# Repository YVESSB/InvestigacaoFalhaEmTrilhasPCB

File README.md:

# Identificação de curto-circuito em circuito impresso utilizando ESPECTROSCOPIA DE IMPEDÂNICA ELÉTRICA

Palavras-chave:
 * ESPECTROSCOPIA DE IMPEDÂNICA ELÉTRICA
 * DETECÇÃO DE FALHAS
 * PLACA DE CIRCUITO IMPRESSO - PCI | PCB

Nesta página são fornecidos dados e documentos referente a análise de dados. Informações utilizadas no trabalho de mestrado e com o objetivo de identificar potencial curto-circuito em um circuito impresso, por meio da espectroscopia de impedância elétrica

Observações:

* Para os programas disponíveis na pasta '2 - Programas', os arquivos de dados devem estar no mesmo ambiente (disponíveis em '1 - DadosAnalisados').
* Programas desenvolvidos em Python, com Jupyter Notebook.

## Introdução 

Para o a identificação de possíveis curto-circuito utilizando a espectroscopia de impedância elétrica, diferentes trilhas em placas de circuito impresso foram medidas utilizando um espectrômetro.

<div align="center">

</div>

As trilhas medidas estavam em placas de circuitos impresso feita de fenolite, e que tinham parâmetros alterados de em função de comprimento, distancia de isolamento e nível do potencial curto-circuito.

<div align="center">

</div>

## Resultados

### Análise qualitativa com gráficos de Bode e dendrogramas
Os dados obtidos das medições foram fundamental para a validaçãode que a espectroscopia pode ser utilizada como técnica para identificação de potenciais curtos-circuitos em placas de circuito impresso (PCIs ou PCBs), por meio da análise qualitativa ou quantitativa. A seguir são apresentado gráficos de dispersão e dendrograma das medições de trilhas de espessura de 0,75mm e isolamento de 1,5mm, onde é possível identificar que há um  agrupamento e tendência da separação de trilhas com potenciais curto-circuito em comparação a uma trilha sem defeito.

<div align="center">

</div>

### Análise quantitativa por meio de algoritmos - aprendizado de máquina
 Com os dados obtidos, foram quasificados dados de trilhas SEM falhas e COM falhas. Se tratamdo de dados advindos de um problema multivariável, a constatação de correlação por aprendizado de máquina é uma solução, para validação de problemas.

<div align="center">

</div>

## Referência

* BORGES, Yves Santos. Análise de curto-circuito em trilhas de circuito impresso utilizando espectroscopia de impedância elétrica. 2023. 1 recurso on-line (70 p. Dissertação (Mestrado Profissional)-Universidade do Estado de Santa Catarina, Programa de Pós-Graduação em Engenharia Elétrica, 2023. Disponível em: http://sistemabu.udesc.br/pergamumweb/vinculos/0000b5/0000b540.pdf. Acesso em: 21 nov. 2023.

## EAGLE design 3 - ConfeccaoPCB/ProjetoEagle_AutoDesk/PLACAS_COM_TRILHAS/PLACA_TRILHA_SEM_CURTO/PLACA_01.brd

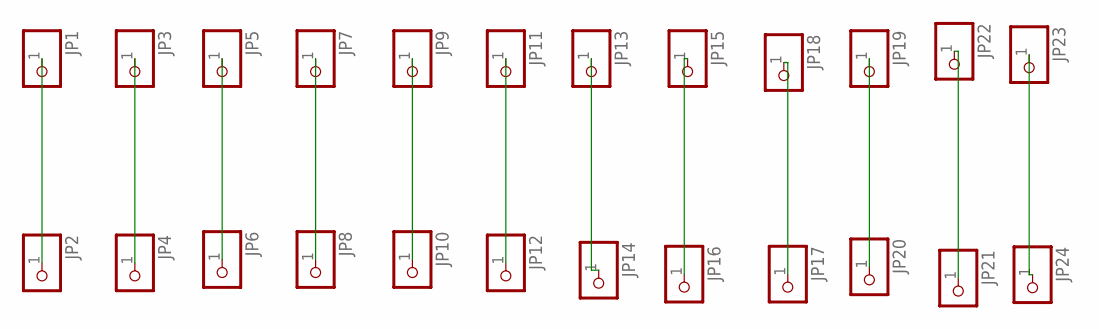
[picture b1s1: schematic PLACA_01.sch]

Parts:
JP1, JP2, JP3, JP4, JP5, JP6, JP7, JP8, JP9, JP10, JP11, JP12, JP13, JP14, JP15, JP16, JP17, JP18, JP19, JP20, JP21, JP22, JP23, JP24: PINHD-1X1; 1X01

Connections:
unnamed: JP1.1, JP2.1
unnamed: JP3.1, JP4.1
unnamed: JP5.1, JP6.1
unnamed: JP7.1, JP8.1
unnamed: JP9.1, JP10.1
unnamed: JP11.1, JP12.1
unnamed: JP13.1, JP14.1
unnamed: JP15.1, JP16.1
unnamed: JP17.1, JP18.1
unnamed: JP19.1, JP20.1
unnamed: JP21.1, JP22.1
unnamed: JP23.1, JP24.1

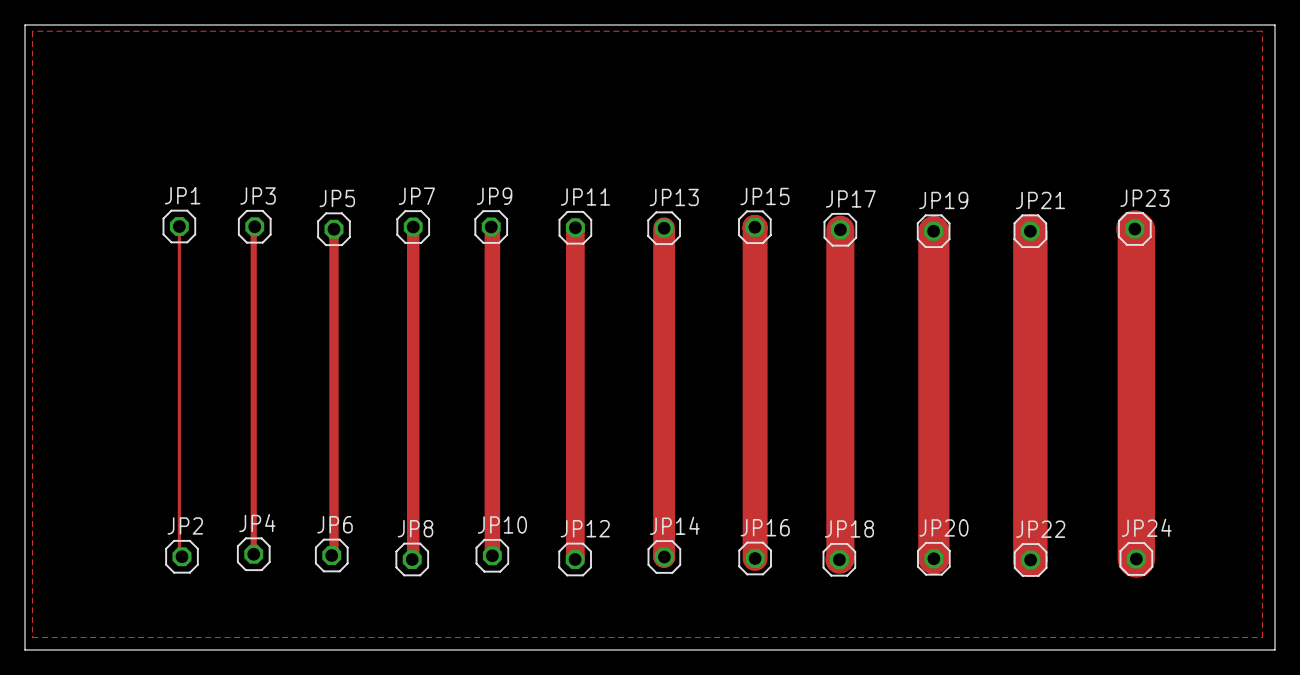
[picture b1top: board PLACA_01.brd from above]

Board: 2 copper layers, 100.0 x 50.0 mm, 24 parts (0 on the bottom side), 12 nets.

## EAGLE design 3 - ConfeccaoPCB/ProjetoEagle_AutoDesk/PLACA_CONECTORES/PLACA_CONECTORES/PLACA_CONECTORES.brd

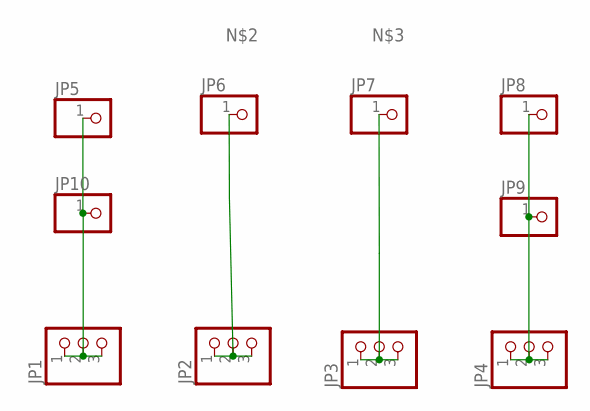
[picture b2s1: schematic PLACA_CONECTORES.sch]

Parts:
JP1, JP2, JP3, JP4: PINHD-1X3/90; 1X03/90
JP5, JP6, JP7, JP8, JP9, JP10: PINHD-1X1; 1X01

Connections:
unnamed: JP1.1, JP1.2, JP1.3, JP5.1, JP10.1
unnamed: JP2.1, JP2.2, JP2.3, JP6.1
unnamed: JP3.1, JP3.2, JP3.3, JP7.1
unnamed: JP4.1, JP4.2, JP4.3, JP8.1, JP9.1

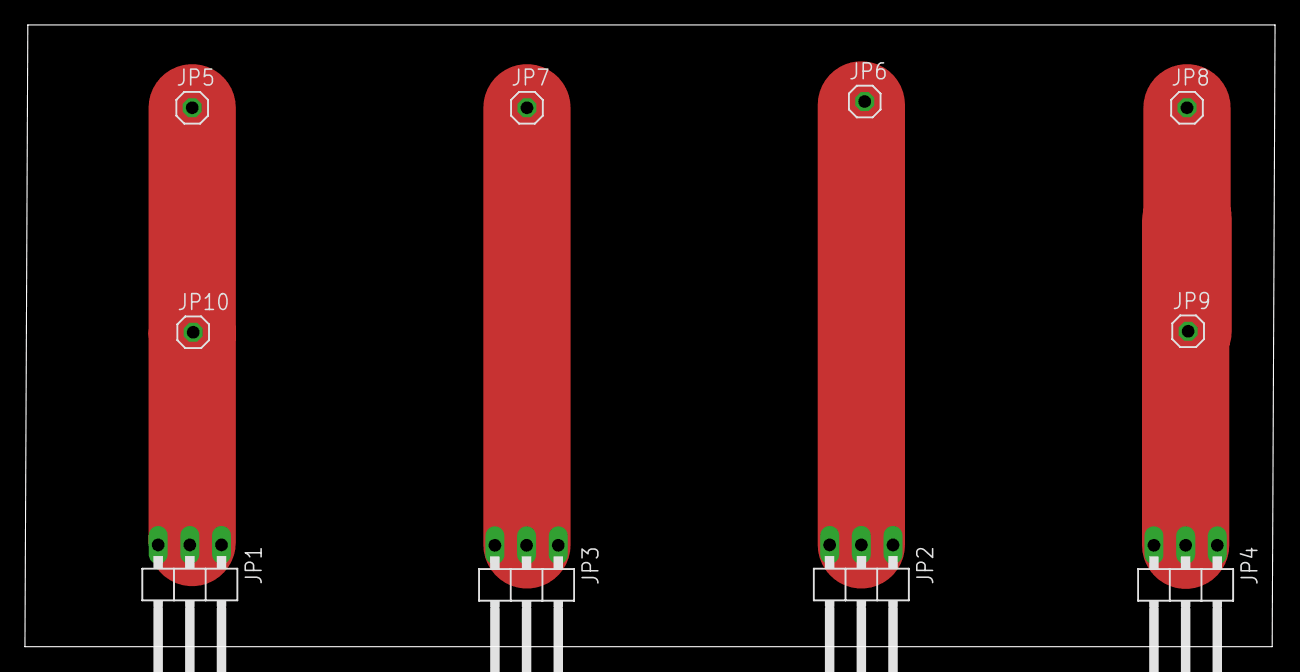
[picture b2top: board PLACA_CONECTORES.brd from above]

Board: 2 copper layers, 100.2 x 49.9 mm, 10 parts (0 on the bottom side), 4 nets.

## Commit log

2023-06-21 Add files via upload
    * Arquivos criados em Python, em ambiente Jupyter Notebook.
    ** Para execultar os programas, os documentos de analise de dados em bloco de nota (.txt), devem estar na mesma pasta desses arquivos.
2023-06-21 Add files upload
